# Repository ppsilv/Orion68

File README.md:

# Orion68
Orion68 a litle system for mc68000

-software

|--dev

|    |--kernel -----> Ambiente de compilação do kernel e de aplicações para o kernel usando libc_pic

|    |--orioncore---> Ambiente de compilação do orioncor e de aplicações para o orioncore usando libcbios nopic

|--include

|--lib

|--libs

     |--libc_pic
     
     |--libm68
     
     |--liborion

2025/10/12: aparentemente essa foi a última versão que kernel carregou e rodou duart.elf

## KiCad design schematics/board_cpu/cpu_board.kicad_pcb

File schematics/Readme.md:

Terminação Passiva no Backplane:

    Mantenha o barramento "limpo" nas placas periféricas.
    No final do barramento físico (Slot 9), coloque as redes resistivas de 10k.
    Isso garante que, mesmo com o Orion68K vazio, os sinais críticos de controle não fiquem flutuando.

A Interface de Disco (MIDE/IDE):

    Hardware: Dois 74HC245 fazendo a ponte entre o barramento de dados do 68000 e o conector IDE.
    Byte-Swap: Desenhe as conexões invertidas entre os 245 e o conector (D15-D8 do 68k no D7-D0 do IDE).
    Atenção: No esquema, coloque uma nota bem visível sobre essa inversão para que, no futuro, você saiba que o acesso aos registros de 8 bits do IDE será feito via endereços pares (UDS ativo).

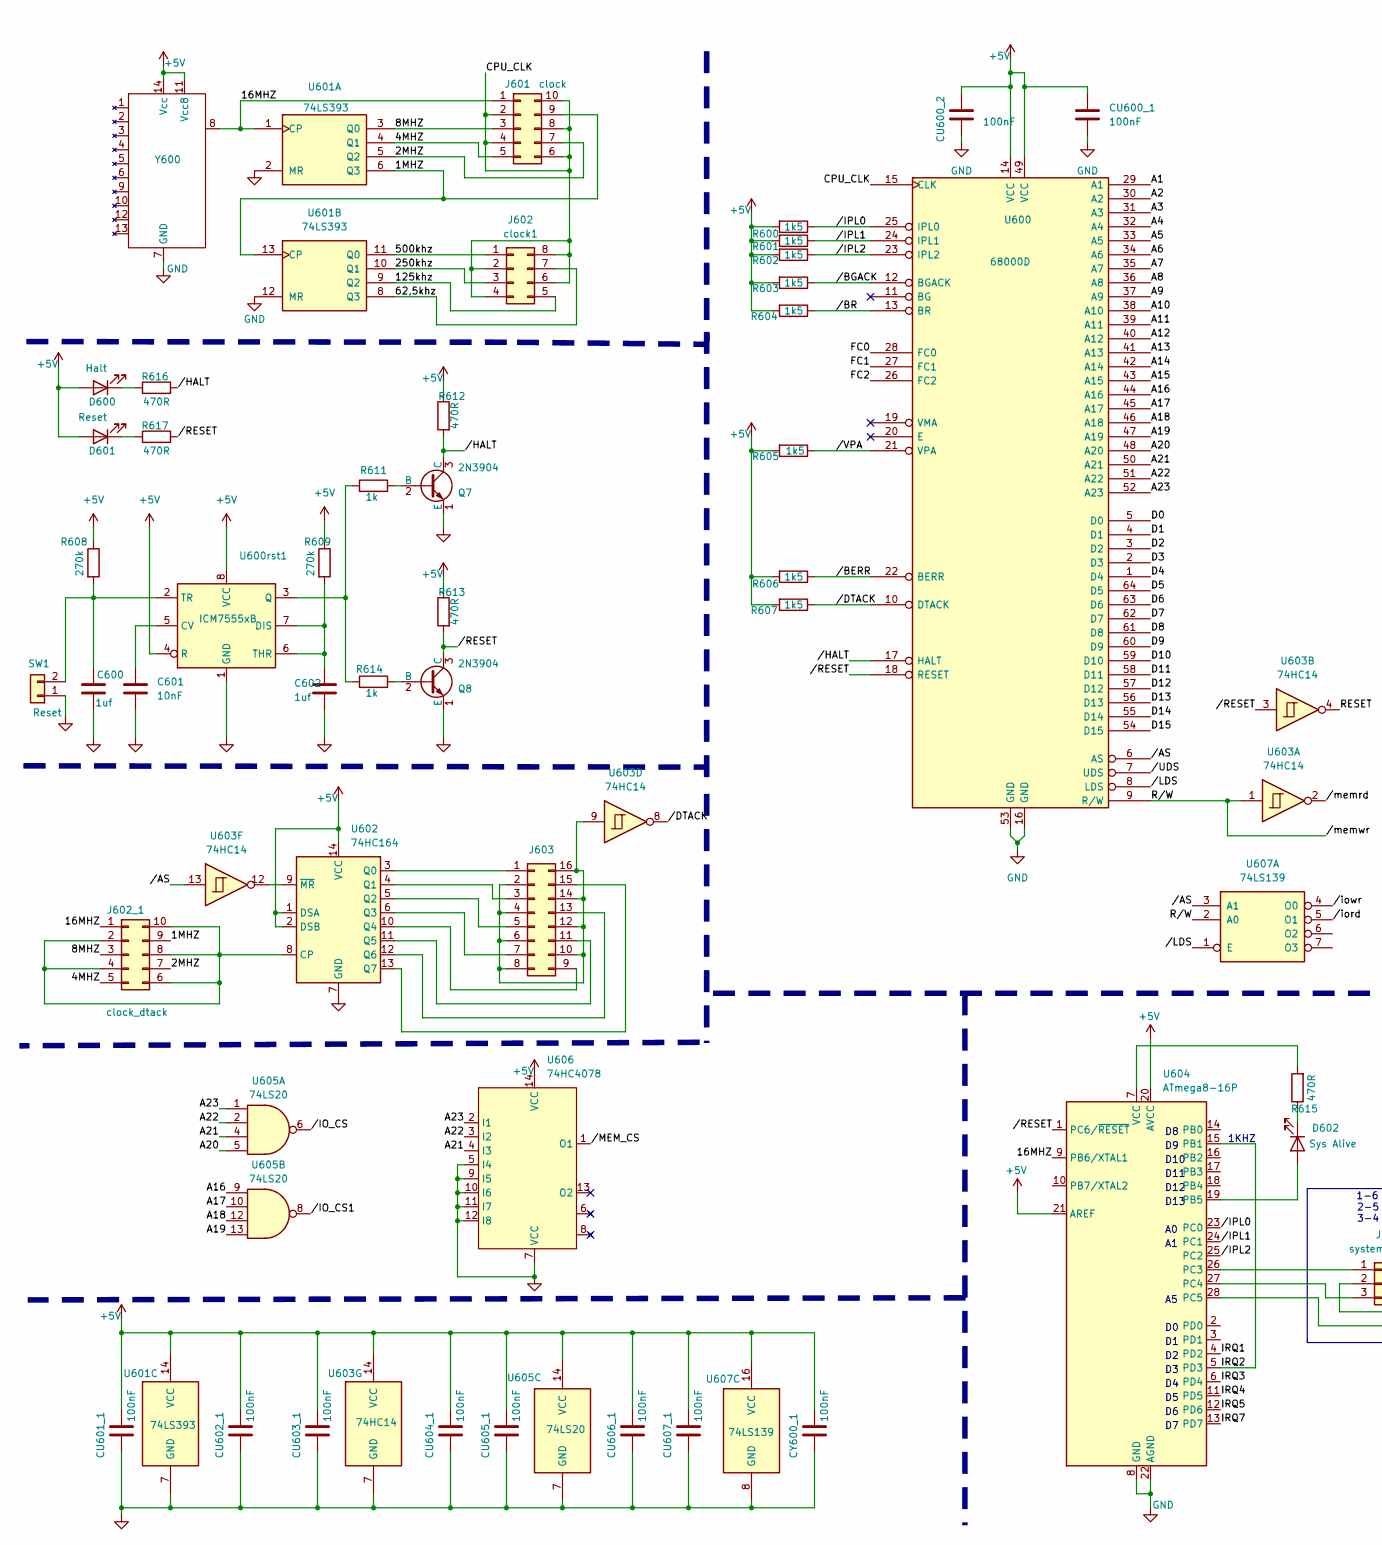
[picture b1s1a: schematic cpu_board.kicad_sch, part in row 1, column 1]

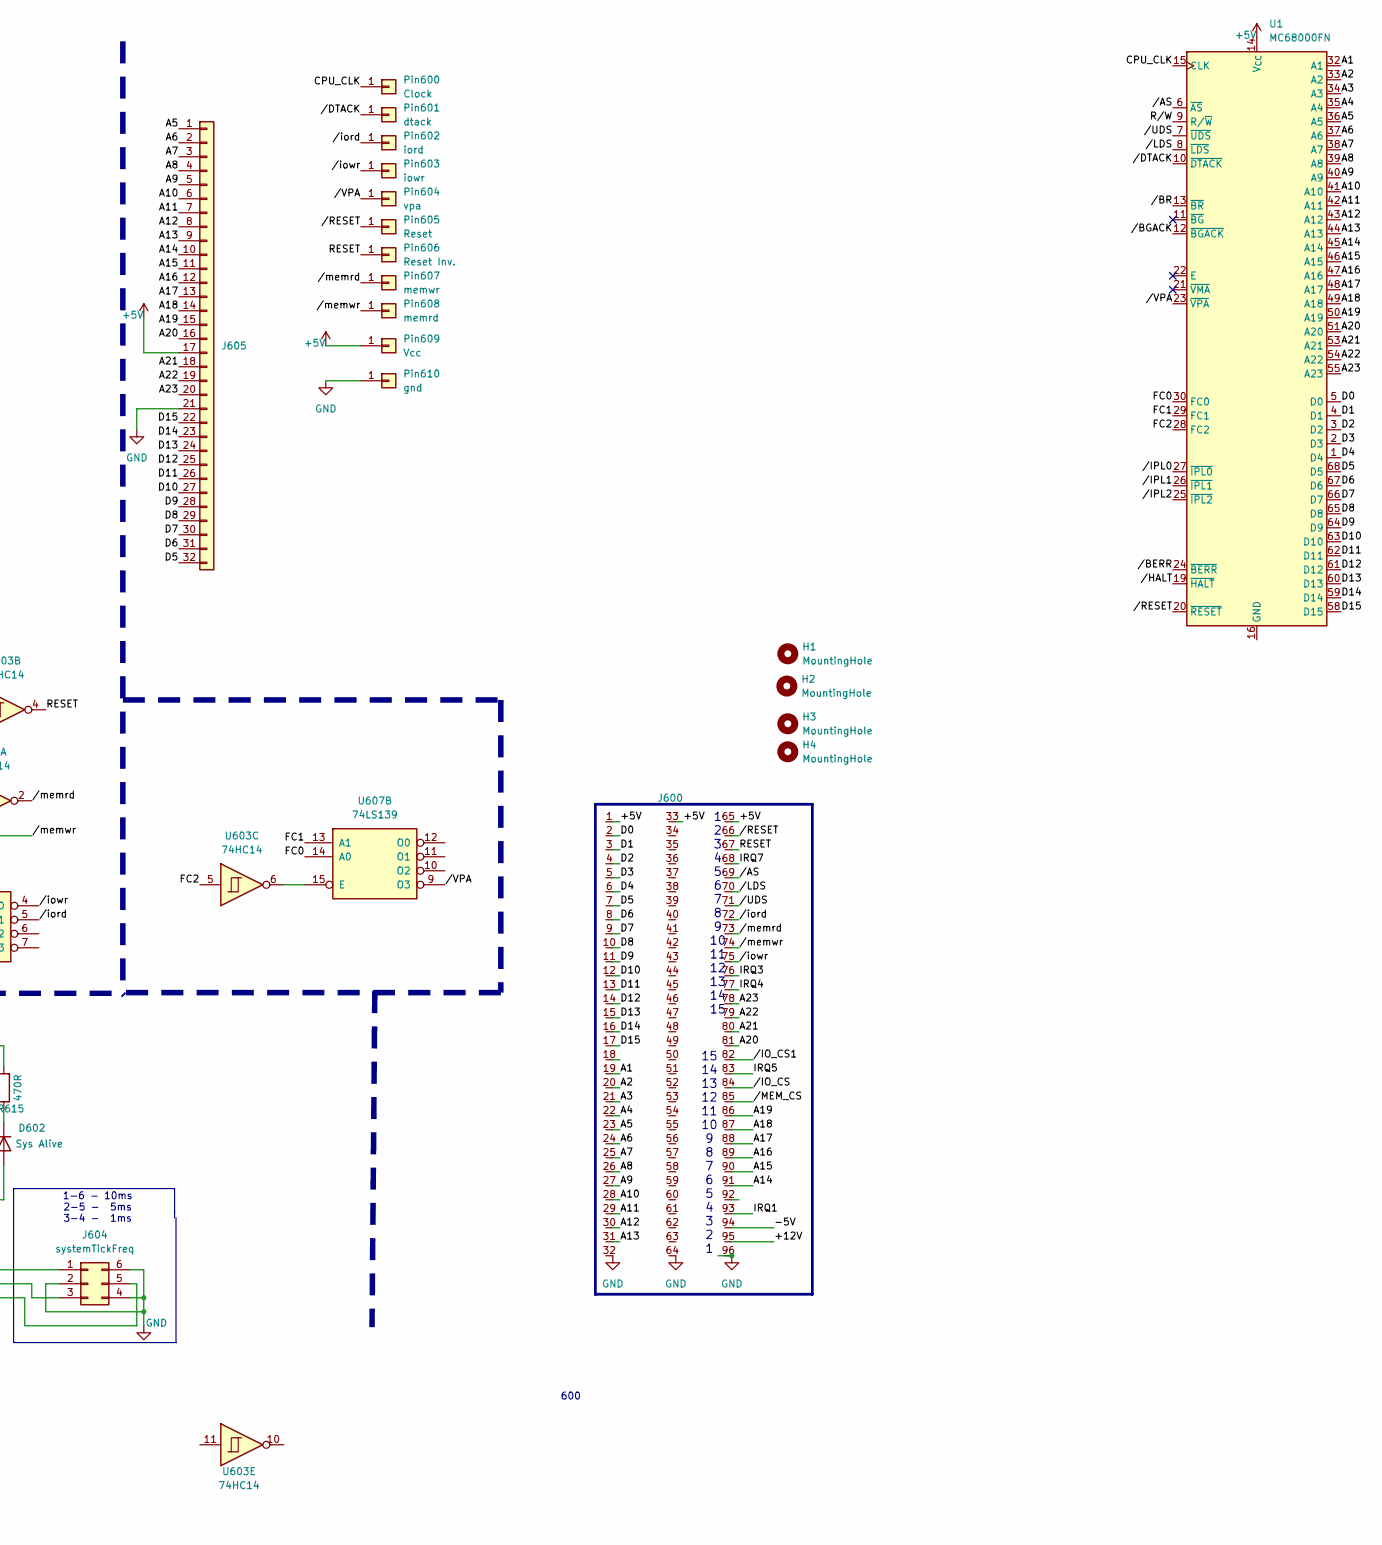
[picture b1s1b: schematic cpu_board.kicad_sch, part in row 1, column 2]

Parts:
C600, C602: 1uf; CP_Radial_D8.0mm_P3.50mm
C601: 10nF; C_0603_1608Metric
CU600_1, CU600_2, CU601_1, CU602_1, CU603_1, CU604_1, CU605_1, CU606_1, CU607_1: 100nF; C_0805_2012Metric
CY600_1: 100nF; C_0805_2012Metric
D600: Halt; PinHeader_1x02_P2.54mm_Vertical
D601: Reset; PinHeader_1x02_P2.54mm_Vertical
D602: Sys Alive; PinHeader_1x02_P2.54mm_Vertical
H1, H2: MountingHole; MountingHole_3.2mm_M3
H3, H4: MountingHole; MountingHole_2.1mm
J600: Euro96pin; conn_euro96
J601: clock; PinHeader_2x05_P2.54mm_Vertical
J602: clock1; PinHeader_2x04_P2.54mm_Vertical
J602_1: clock_dtack; PinHeader_2x05_P2.54mm_Vertical
J603: Conn_02x08_Counter_Clockwise; PinHeader_2x08_P2.54mm_Vertical
J604: systemTickFreq; PinHeader_2x03_P2.54mm_Vertical
J605: Conn_01x32; PinHeader_1x32_P2.54mm_Vertical
Pin600: Clock; PinHeader_1x01_P2.54mm_Vertical
Pin601: dtack; PinHeader_1x01_P2.54mm_Vertical
Pin602: iord; PinHeader_1x01_P2.54mm_Vertical
Pin603: iowr; PinHeader_1x01_P2.54mm_Vertical
Pin604: vpa; PinHeader_1x01_P2.54mm_Vertical
Pin605: Reset; PinHeader_1x01_P2.54mm_Vertical
Pin606: Reset Inv.; PinHeader_1x01_P2.54mm_Vertical
Pin607: memwr; PinHeader_1x01_P2.54mm_Vertical
Pin608: memrd; PinHeader_1x01_P2.54mm_Vertical
Pin609: Vcc; PinHeader_1x01_P2.54mm_Vertical
Pin610: gnd; PinHeader_1x01_P2.54mm_Vertical
Q7, Q8: 2N3904; TO-92_Inline
R600, R601, R602, R603, R604, R605, R606, R607: 1k5; R_0805_2012Metric
R608, R609: 270k; R_Axial_DIN0204_L3.6mm_D1.6mm_P5.08mm_Horizontal
R611, R614: 1k; R_Axial_DIN0204_L3.6mm_D1.6mm_P5.08mm_Horizontal
R612, R613, R615, R616, R617: 470R; R_Axial_DIN0204_L3.6mm_D1.6mm_P5.08mm_Horizontal
SW1: Reset; PinHeader_1x02_P2.54mm_Vertical
U1: MC68000FN; PLCC-68_THT-Socket
U600: 68000D; DIP-64_W22.86mm
U600rst1: ICM7555xB; DIP-8_W7.62mm
U601: 74LS393; DIP-14_W7.62mm
U602: 74HC164; DIP-14_W7.62mm
U603: 74HC14; DIP-14_W7.62mm
U604: ATmega8-16P; DIP-28_W7.62mm
U605: 74LS20; DIP-14_W7.62mm
U606: 74HC4078; DIP-14_W7.62mm
U607: 74LS139; DIP-16_W7.62mm
Y600: DIP-14_W7.62mm

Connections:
+5V: CU600_1.1, CU600_2.1, CU601_1.1, CU602_1.1, CU603_1.1, CU604_1.1, CU605_1.1, CU606_1.1, CU607_1.1, CY600_1.1, D600.2 (A), D601.2 (A), J600.1, J600.33, J600.65, J605.17, Pin609.1, R600.2, R601.2, R602.2, R603.2, R604.2, R605.2, R606.2, R607.2, R608.1, R609.1, R612.1, R613.1, U1.14 (V_{CC}), U1.52 (V_{CC}), U600.14 (VCC), U600.49 (VCC), U600rst1.4 (R), U600rst1.8 (VCC), U601.14 (VCC), U602.1 (DSA), U602.2 (DSB), U602.14 (VCC), U603.14 (VCC), U604.20 (AVCC), U604.21 (AREF), U605.14 (VCC), U606.14 (VCC), U607.16 (VCC), Y600.11 (Vcc8), Y600.14 (Vcc)
/1MHZ: J601.9, J602_1.9, U601.6 (Q3), U601.13 (CP)
/2MHZ: J601.7, J602_1.7, U601.5 (Q2)
/4MHZ: J601.5, J602_1.5, U601.4 (Q1)
/8MHZ: J601.3, J602_1.3, U601.3 (Q0)
/16MHZ: J601.1, J602_1.1, U601.1 (CP), U604.9 (PB6/XTAL1), Y600.8
/62,5khz: J602.7, U601.8 (Q3)
/125khz: J602.5, U601.9 (Q2)
/250khz: J602.3, U601.10 (Q1)
/500khz: J602.1, U601.11 (Q0)
/+12V: J600.95
/-5V: J600.94
/A1: J600.19, U1.32 (A1), U600.29 (A1)
/A2: J600.20, U1.33 (A2), U600.30 (A2)
/A3: J600.21, U1.34 (A3), U600.31 (A3)
/A4: J600.22, U1.35 (A4), U600.32 (A4)
/A5: J600.23, J605.1, U1.36 (A5), U600.33 (A5)
/A6: J600.24, J605.2, U1.37 (A6), U600.34 (A6)
/A7: J600.25, J605.3, U1.38 (A7), U600.35 (A7)
/A8: J600.26, J605.4, U1.39 (A8), U600.36 (A8)
/A9: J600.27, J605.5, U1.40 (A9), U600.37 (A9)
/A10: J600.28, J605.6, U1.41 (A10), U600.38 (A10)
/A11: J600.29, J605.7, U1.42 (A11), U600.39 (A11)
/A12: J600.30, J605.8, U1.43 (A12), U600.40 (A12)
/A13: J600.31, J605.9, U1.44 (A13), U600.41 (A13)
/A14: J600.91, J605.10, U1.45 (A14), U600.42 (A14)
/A15: J600.90, J605.11, U1.46 (A15), U600.43 (A15)
/A16: J600.89, J605.12, U1.47 (A16), U600.44 (A16), U605.9
/A17: J600.88, J605.13, U1.48 (A17), U600.45 (A17), U605.10
/A18: J600.87, J605.14, U1.49 (A18), U600.46 (A18), U605.12
/A19: J600.86, J605.15, U1.50 (A19), U600.47 (A19), U605.13
/A20: J600.81, J605.16, U1.51 (A20), U600.48 (A20), U605.5
/A21: J600.80, J605.18, U1.53 (A21), U600.50 (A21), U605.4, U606.4 (I3)
/A22: J600.79, J605.19, U1.54 (A22), U600.51 (A22), U605.2, U606.3 (I2)
/A23: J600.78, J605.20, U1.55 (A23), U600.52 (A23), U605.1, U606.2 (I1)
/CPU_CLK: J601.2, J601.4, J601.6, J601.8, J601.10, J602.2, J602.4, J602.6, J602.8, Pin600.1, U1.15 (CLK), U600.15 (CLK)
/D0: J600.2, U1.5 (D0), U600.5 (D0)
/D1: J600.3, U1.4 (D1), U600.4 (D1)
/D2: J600.4, U1.3 (D2), U600.3 (D2)
/D3: J600.5, U1.2 (D3), U600.2 (D3)
/D4: J600.6, U1.1 (D4), U600.1 (D4)
/D5: J600.7, J605.32, U1.68 (D5), U600.64 (D5)
/D6: J600.8, J605.31, U1.67 (D6), U600.63 (D6)
/D7: J600.9, J605.30, U1.66 (D7), U600.62 (D7)
/D8: J600.10, J605.29, U1.65 (D8), U600.61 (D8)
/D9: J600.11, J605.28, U1.64 (D9), U600.60 (D9)
/D10: J600.12, J605.27, U1.63 (D10), U600.59 (D10)
/D11: J600.13, J605.26, U1.62 (D11), U600.58 (D11)
/D12: J600.14, J605.25, U1.61 (D12), U600.57 (D12)
/D13: J600.15, J605.24, U1.60 (D13), U600.56 (D13)
/D14: J600.16, J605.23, U1.59 (D14), U600.55 (D14)
/D15: J600.17, J605.22, U1.58 (D15), U600.54 (D15)
/FC0: U1.30 (FC0), U600.28 (FC0), U607.14 (A0)
/FC1: U1.29 (FC1), U600.27 (FC1), U607.13 (A1)
/FC2: U1.28 (FC2), U600.26 (FC2), U603.5
/IRQ1: J600.93, U604.4 (PD2)
/IRQ2: U604.5 (PD3), U604.15 (PB1)
/IRQ3: J600.76, U604.6 (PD4)
/IRQ4: J600.77, U604.11 (PD5)
/IRQ5: J600.83, U604.12 (PD6)
/IRQ7: J600.68, U604.13 (PD7)
/RESET: J600.67, Pin606.1, U603.4
/R/W: J600.74, Pin608.1, U1.9 (R/~W), U600.9 (R/W), U603.1, U607.2 (A0)
//AS: J600.69, U1.6 (~AS), U600.6 (AS), U603.13, U607.3 (A1)
//BERR: R606.1, U1.24 (~BERR), U600.22 (BERR)
//BGACK: R603.1, U1.12 (~BGACK), U600.12 (BGACK)
//BR: R604.1, U1.13 (~BR), U600.13 (BR)
//DTACK: Pin601.1, R607.1, U1.10 (~DTACK), U600.10 (DTACK), U603.8
//HALT: Q7.3 (C), R612.2, R616.2, U1.19 (~HALT), U600.17 (HALT)
//IO_CS: J600.84, U605.6
//IO_CS1: J600.82, U605.8
//IPL0: R600.1, U1.27 (~IPL0), U600.25 (IPL0), U604.23 (PC0)
//IPL1: R601.1, U1.26 (~IPL1), U600.24 (IPL1), U604.24 (PC1)
//IPL2: R602.1, U1.25 (~IPL2), U600.23 (IPL2), U604.25 (PC2)
//LDS: J600.70, U1.8 (~LDS), U600.8 (LDS), U607.1 (E)
//MEM_CS: J600.85, U606.1 (O1)
//RESET: J600.66, Pin605.1, Q8.3 (C), R613.2, R617.2, U1.20 (~RESET), U600.18 (RESET), U603.3, U604.1 (PC6/~RESET)
//UDS: J600.71, U1.7 (~UDS), U600.7 (UDS)
//VPA: Pin604.1, R605.1, U1.23 (~VPA), U600.21 (VPA), U607.9 (O3)
//iord: J600.72, Pin602.1, U607.5 (O1)
//iowr: J600.75, Pin603.1, U607.4 (O0)
//memrd: J600.73, Pin607.1, U603.2
GND: C600.2, C601.2, C602.2, CU600_1.2, CU600_2.2, CU601_1.2, CU602_1.2, CU603_1.2, CU604_1.2, CU605_1.2, CU606_1.2, CU607_1.2, CY600_1.2, J600.32, J600.64, J600.96, J604.2, J604.4, J604.6, J605.21, Pin610.1, Q7.1 (E), Q8.1 (E), SW1.1, U600.16 (GND), U600.53 (GND), U600rst1.1 (GND), U601.2 (MR), U601.7 (GND), U601.12 (MR), U602.7 (GND), U603.7 (GND), U604.8 (GND), U604.22 (AGND), U605.7 (GND), U606.5 (I4), U606.7 (VCC), U606.9 (I5), U606.10 (I6), U606.11 (I7), U606.12 (I8), U607.8 (GND), Y600.7 (GND)
unnamed: D600.1 (K), R616.1
unnamed: D601.1 (K), R617.1
unnamed: D602.2 (A), U604.19 (PB5)
unnamed: D602.1 (K), R615.1
unnamed: J602_1.2, J602_1.4, J602_1.6, J602_1.8, J602_1.10, U602.8 (CP)
unnamed: J603.1, U602.3 (Q0)
unnamed: J603.3, U602.4 (Q1)
unnamed: J603.5, U602.5 (Q2)
unnamed: J603.7, U602.6 (Q3)
unnamed: J603.9, U602.10 (Q4)
unnamed: J603.2, J603.4, J603.6, J603.8, J603.10, J603.12, J603.14, J603.16, U603.9
unnamed: J603.11, U602.11 (Q5)
unnamed: J603.13, U602.12 (Q6)
unnamed: J603.15, U602.13 (Q7)
unnamed: J604.1, U604.26 (PC3)
unnamed: J604.3, U604.27 (PC4)
unnamed: J604.5, U604.28 (PC5)
unnamed: Q7.2 (B), R611.1
unnamed: Q8.2 (B), R614.1
unnamed: C600.1, R608.2, SW1.2, U600rst1.2 (TR)
unnamed: U1.16 (GND), U1.17 (GND), U1.56 (GND), U1.57 (GND)
unnamed: C601.1, U600rst1.5 (CV)
unnamed: C602.1, R609.2, U600rst1.6 (THR), U600rst1.7 (DIS)
unnamed: R611.2, R614.2, U600rst1.3 (Q)
unnamed: U602.9 (~MR), U603.12
unnamed: R615.2, U604.7 (VCC)
unnamed: U603.6, U607.15 (E)

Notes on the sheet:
1 2 3 4 5 6 7 8 9 10 11 12 13 14 15
15 14 13 12 11 10 9 8 7 6 5 4 3 2 1
600
1KHZ
D11
D13
1-6 - 10ms 2-5 - 5ms 3-4 - 1ms
D12
D10

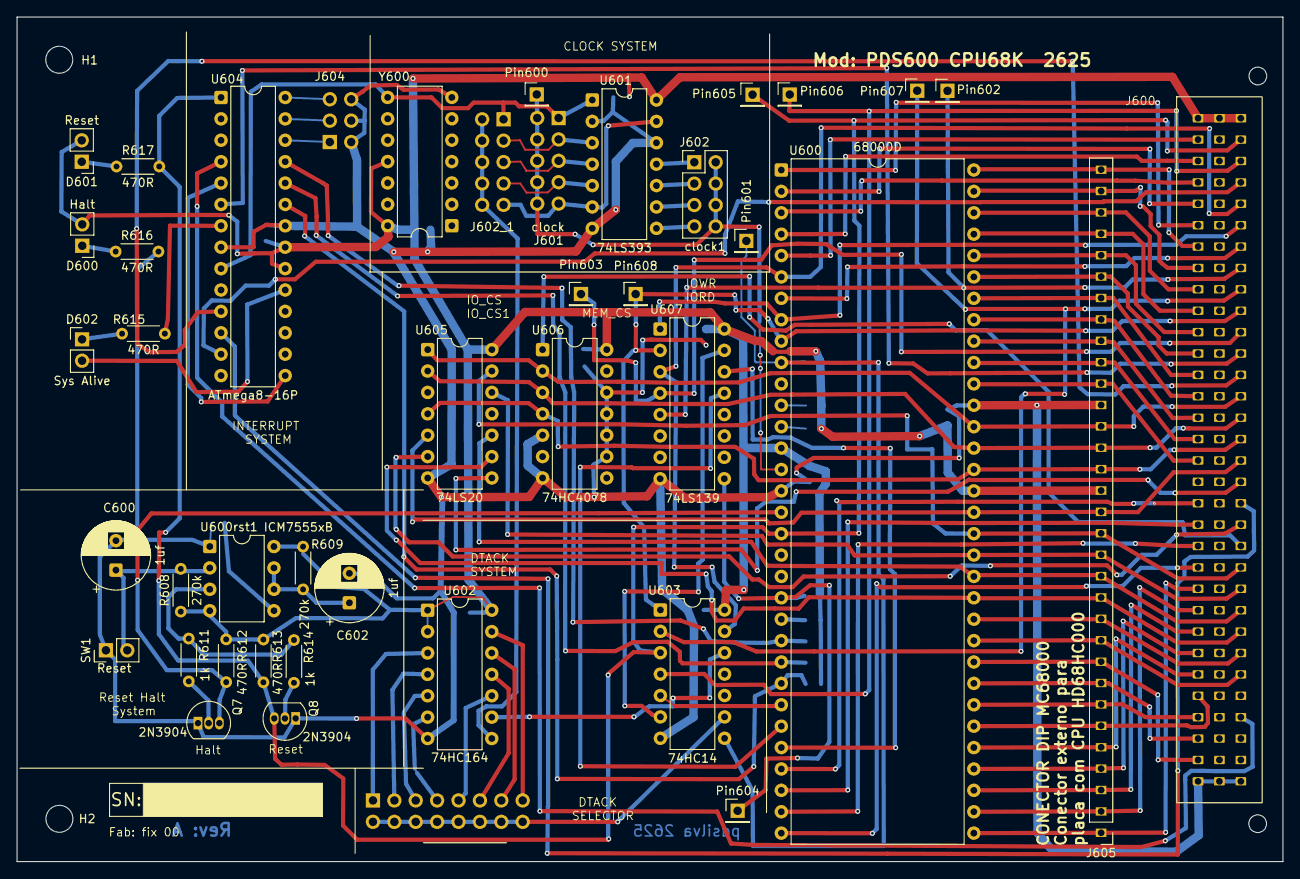
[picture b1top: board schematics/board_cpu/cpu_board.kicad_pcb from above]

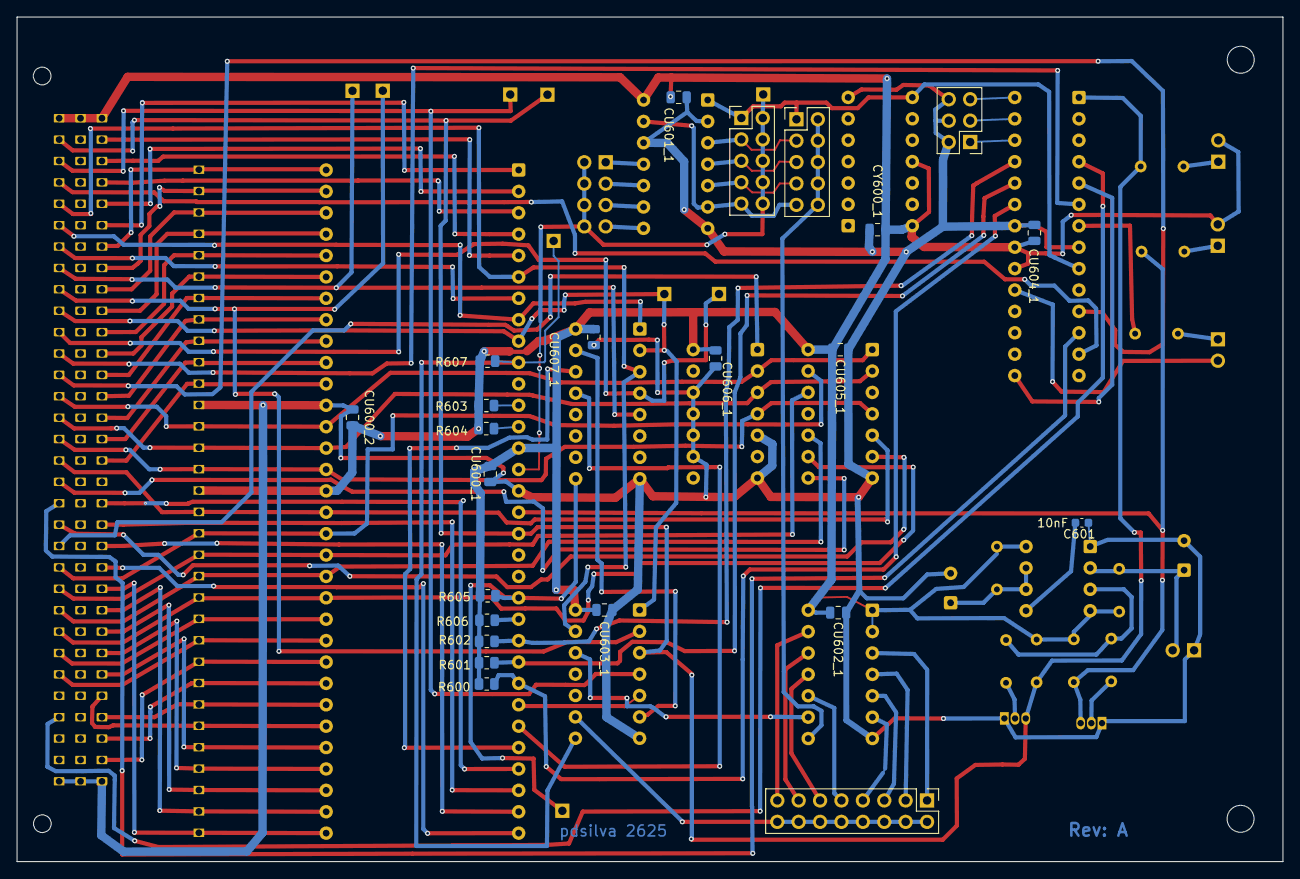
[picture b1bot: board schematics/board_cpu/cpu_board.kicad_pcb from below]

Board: 2 copper layers, 150.3 x 100.3 mm, 66 parts (23 on the bottom side), 107 nets.

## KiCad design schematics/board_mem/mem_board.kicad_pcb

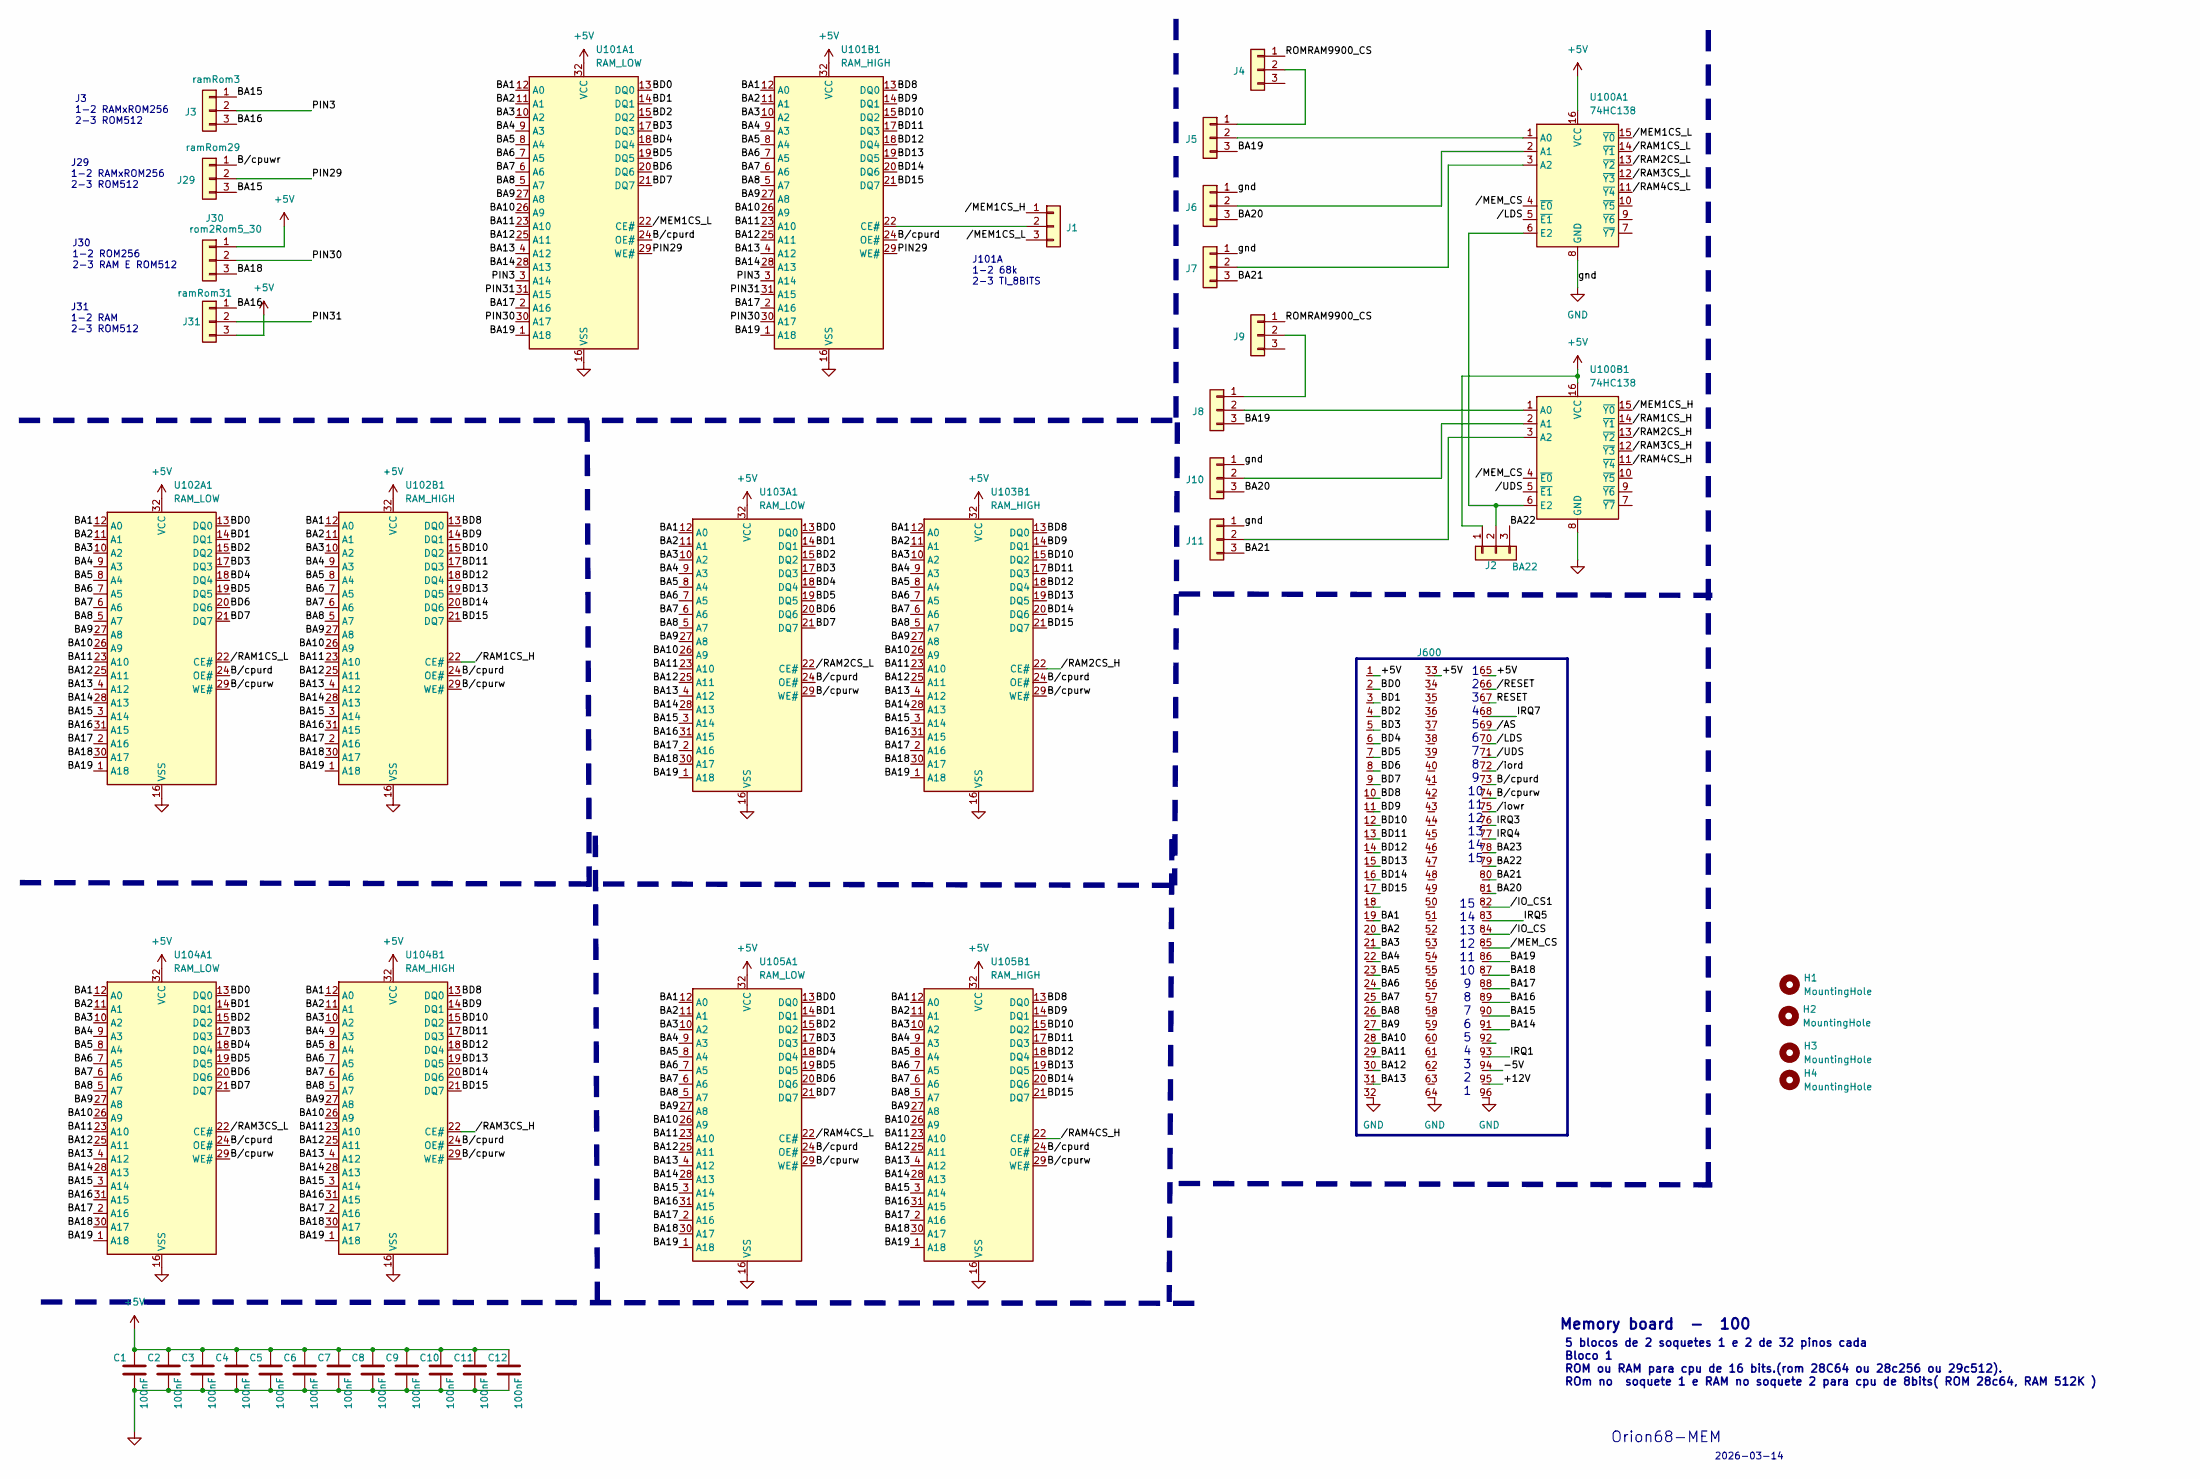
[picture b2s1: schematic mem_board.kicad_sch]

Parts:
C1, C2, C3, C4, C5, C6, C7, C8, C9, C10, C11, C12: 100nF; C_0805_2012Metric_Pad1.18x1.45mm_HandSolder
H1, H2: MountingHole; MountingHole_3.2mm_M3
H3, H4: MountingHole; MountingHole_2.1mm
J1: J101A; PinHeader_1x03_P2.54mm_Vertical
J2: BA22; PinHeader_1x03_P2.54mm_Vertical
J3: ramRom3; PinHeader_1x03_P2.54mm_Vertical
J4, J5, J8, J9: J100A; PinHeader_1x03_P2.54mm_Vertical
J6, J10: J100B; PinHeader_1x03_P2.54mm_Vertical
J7, J11: J100C; PinHeader_1x03_P2.54mm_Vertical
J29: ramRom29; PinHeader_1x03_P2.54mm_Vertical
J30: rom2Rom5_30; PinHeader_1x03_P2.54mm_Vertical
J31: ramRom31; PinHeader_1x03_P2.54mm_Vertical
J600: Euro96pin; conn_euro96
U100A1, U100B1: 74HC138; DIP-16_W7.62mm
U101A1, U102A1, U103A1, U104A1, U105A1: RAM_LOW; DIP-32_W15.24mm
U101B1, U102B1, U103B1, U104B1, U105B1: RAM_HIGH; DIP-32_W15.24mm

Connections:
+5V: C1.1, C2.1, C3.1, C4.1, C5.1, C6.1, C7.1, C8.1, C9.1, C10.1, C11.1, C12.1, J2.1, J30.1, J31.3, J600.1, J600.33, J600.65, U100A1.16 (VCC), U100B1.16 (VCC), U101A1.32 (VCC), U101B1.32 (VCC), U102A1.32 (VCC), U102B1.32 (VCC), U103A1.32 (VCC), U103B1.32 (VCC), U104A1.32 (VCC), U104B1.32 (VCC), U105A1.32 (VCC), U105B1.32 (VCC)
/+12V: J600.95
/-5V: J600.94
/BA1: J600.19, U101A1.12 (A0), U101B1.12 (A0), U102A1.12 (A0), U102B1.12 (A0), U103A1.12 (A0), U103B1.12 (A0), U104A1.12 (A0), U104B1.12 (A0), U105A1.12 (A0), U105B1.12 (A0)
/BA2: J600.20, U101A1.11 (A1), U101B1.11 (A1), U102A1.11 (A1), U102B1.11 (A1), U103A1.11 (A1), U103B1.11 (A1), U104A1.11 (A1), U104B1.11 (A1), U105A1.11 (A1), U105B1.11 (A1)
/BA3: J600.21, U101A1.10 (A2), U101B1.10 (A2), U102A1.10 (A2), U102B1.10 (A2), U103A1.10 (A2), U103B1.10 (A2), U104A1.10 (A2), U104B1.10 (A2), U105A1.10 (A2), U105B1.10 (A2)
/BA4: J600.22, U101A1.9 (A3), U101B1.9 (A3), U102A1.9 (A3), U102B1.9 (A3), U103A1.9 (A3), U103B1.9 (A3), U104A1.9 (A3), U104B1.9 (A3), U105A1.9 (A3), U105B1.9 (A3)
/BA5: J600.23, U101A1.8 (A4), U101B1.8 (A4), U102A1.8 (A4), U102B1.8 (A4), U103A1.8 (A4), U103B1.8 (A4), U104A1.8 (A4), U104B1.8 (A4), U105A1.8 (A4), U105B1.8 (A4)
/BA6: J600.24, U101A1.7 (A5), U101B1.7 (A5), U102A1.7 (A5), U102B1.7 (A5), U103A1.7 (A5), U103B1.7 (A5), U104A1.7 (A5), U104B1.7 (A5), U105A1.7 (A5), U105B1.7 (A5)
/BA7: J600.25, U101A1.6 (A6), U101B1.6 (A6), U102A1.6 (A6), U102B1.6 (A6), U103A1.6 (A6), U103B1.6 (A6), U104A1.6 (A6), U104B1.6 (A6), U105A1.6 (A6), U105B1.6 (A6)
/BA8: J600.26, U101A1.5 (A7), U101B1.5 (A7), U102A1.5 (A7), U102B1.5 (A7), U103A1.5 (A7), U103B1.5 (A7), U104A1.5 (A7), U104B1.5 (A7), U105A1.5 (A7), U105B1.5 (A7)
/BA9: J600.27, U101A1.27 (A8), U101B1.27 (A8), U102A1.27 (A8), U102B1.27 (A8), U103A1.27 (A8), U103B1.27 (A8), U104A1.27 (A8), U104B1.27 (A8), U105A1.27 (A8), U105B1.27 (A8)
/BA10: J600.28, U101A1.26 (A9), U101B1.26 (A9), U102A1.26 (A9), U102B1.26 (A9), U103A1.26 (A9), U103B1.26 (A9), U104A1.26 (A9), U104B1.26 (A9), U105A1.26 (A9), U105B1.26 (A9)
/BA11: J600.29, U101A1.23 (A10), U101B1.23 (A10), U102A1.23 (A10), U102B1.23 (A10), U103A1.23 (A10), U103B1.23 (A10), U104A1.23 (A10), U104B1.23 (A10), U105A1.23 (A10), U105B1.23 (A10)
/BA12: J600.30, U101A1.25 (A11), U101B1.25 (A11), U102A1.25 (A11), U102B1.25 (A11), U103A1.25 (A11), U103B1.25 (A11), U104A1.25 (A11), U104B1.25 (A11), U105A1.25 (A11), U105B1.25 (A11)
/BA13: J600.31, U101A1.4 (A12), U101B1.4 (A12), U102A1.4 (A12), U102B1.4 (A12), U103A1.4 (A12), U103B1.4 (A12), U104A1.4 (A12), U104B1.4 (A12), U105A1.4 (A12), U105B1.4 (A12)
/BA14: J600.91, U101A1.28 (A13), U101B1.28 (A13), U102A1.28 (A13), U102B1.28 (A13), U103A1.28 (A13), U103B1.28 (A13), U104A1.28 (A13), U104B1.28 (A13), U105A1.28 (A13), U105B1.28 (A13)
/BA15: J3.1, J29.3, J600.90, U102A1.3 (A14), U102B1.3 (A14), U103A1.3 (A14), U103B1.3 (A14), U104A1.3 (A14), U104B1.3 (A14), U105A1.3 (A14), U105B1.3 (A14)
/BA16: J3.3, J31.1, J600.89, U102A1.31 (A15), U102B1.31 (A15), U103A1.31 (A15), U103B1.31 (A15), U104A1.31 (A15), U104B1.31 (A15), U105A1.31 (A15), U105B1.31 (A15)
/BA17: J600.88, U101A1.2 (A16), U101B1.2 (A16), U102A1.2 (A16), U102B1.2 (A16), U103A1.2 (A16), U103B1.2 (A16), U104A1.2 (A16), U104B1.2 (A16), U105A1.2 (A16), U105B1.2 (A16)
/BA18: J30.3, J600.87, U102A1.30 (A17), U102B1.30 (A17), U103A1.30 (A17), U103B1.30 (A17), U104A1.30 (A17), U104B1.30 (A17), U105A1.30 (A17), U105B1.30 (A17)
/BA19: J5.3, J8.3, J600.86, U101A1.1 (A18), U101B1.1 (A18), U102A1.1 (A18), U102B1.1 (A18), U103A1.1 (A18), U103B1.1 (A18), U104A1.1 (A18), U104B1.1 (A18), U105A1.1 (A18), U105B1.1 (A18)
/BA20: J6.3, J10.3, J600.81
/BA21: J7.3, J11.3, J600.80
/BA22: J2.3, J600.79
/BA23: J600.78
/BD0: J600.2, U101A1.13 (DQ0), U102A1.13 (DQ0), U103A1.13 (DQ0), U104A1.13 (DQ0), U105A1.13 (DQ0)
/BD1: J600.3, U101A1.14 (DQ1), U102A1.14 (DQ1), U103A1.14 (DQ1), U104A1.14 (DQ1), U105A1.14 (DQ1)
/BD2: J600.4, U101A1.15 (DQ2), U102A1.15 (DQ2), U103A1.15 (DQ2), U104A1.15 (DQ2), U105A1.15 (DQ2)
/BD3: J600.5, U101A1.17 (DQ3), U102A1.17 (DQ3), U103A1.17 (DQ3), U104A1.17 (DQ3), U105A1.17 (DQ3)
/BD4: J600.6, U101A1.18 (DQ4), U102A1.18 (DQ4), U103A1.18 (DQ4), U104A1.18 (DQ4), U105A1.18 (DQ4)
/BD5: J600.7, U101A1.19 (DQ5), U102A1.19 (DQ5), U103A1.19 (DQ5), U104A1.19 (DQ5), U105A1.19 (DQ5)
/BD6: J600.8, U101A1.20 (DQ6), U102A1.20 (DQ6), U103A1.20 (DQ6), U104A1.20 (DQ6), U105A1.20 (DQ6)
/BD7: J600.9, U101A1.21 (DQ7), U102A1.21 (DQ7), U103A1.21 (DQ7), U104A1.21 (DQ7), U105A1.21 (DQ7)
/BD8: J600.10, U101B1.13 (DQ0), U102B1.13 (DQ0), U103B1.13 (DQ0), U104B1.13 (DQ0), U105B1.13 (DQ0)
/BD9: J600.11, U101B1.14 (DQ1), U102B1.14 (DQ1), U103B1.14 (DQ1), U104B1.14 (DQ1), U105B1.14 (DQ1)
/BD10: J600.12, U101B1.15 (DQ2), U102B1.15 (DQ2), U103B1.15 (DQ2), U104B1.15 (DQ2), U105B1.15 (DQ2)
/BD11: J600.13, U101B1.17 (DQ3), U102B1.17 (DQ3), U103B1.17 (DQ3), U104B1.17 (DQ3), U105B1.17 (DQ3)
/BD12: J600.14, U101B1.18 (DQ4), U102B1.18 (DQ4), U103B1.18 (DQ4), U104B1.18 (DQ4), U105B1.18 (DQ4)
/BD13: J600.15, U101B1.19 (DQ5), U102B1.19 (DQ5), U103B1.19 (DQ5), U104B1.19 (DQ5), U105B1.19 (DQ5)
/BD14: J600.16, U101B1.20 (DQ6), U102B1.20 (DQ6), U103B1.20 (DQ6), U104B1.20 (DQ6), U105B1.20 (DQ6)
/BD15: J600.17, U101B1.21 (DQ7), U102B1.21 (DQ7), U103B1.21 (DQ7), U104B1.21 (DQ7), U105B1.21 (DQ7)
/B/cpurd: J600.73, U101A1.24 (OE#), U101B1.24 (OE#), U102A1.24 (OE#), U102B1.24 (OE#), U103A1.24 (OE#), U103B1.24 (OE#), U104A1.24 (OE#), U104B1.24 (OE#), U105A1.24 (OE#), U105B1.24 (OE#)
/B/cpurw: J600.74, U102A1.29 (WE#), U102B1.29 (WE#), U103A1.29 (WE#), U103B1.29 (WE#), U104A1.29 (WE#), U104B1.29 (WE#), U105A1.29 (WE#), U105B1.29 (WE#)
/B/cpuwr: J29.1
/IRQ1: J600.93
/IRQ3: J600.76
/IRQ4: J600.77
/IRQ5: J600.83
/IRQ7: J600.68
/PIN3: J3.2, U101A1.3 (A14), U101B1.3 (A14)
/PIN29: J29.2, U101A1.29 (WE#), U101B1.29 (WE#)
/PIN30: J30.2, U101A1.30 (A17), U101B1.30 (A17)
/PIN31: J31.2, U101A1.31 (A15), U101B1.31 (A15)
/RESET: J600.67
/ROMRAM9900_CS: J4.1, J9.1
//AS: J600.69
//IO_CS: J600.84
//IO_CS1: J600.82
//LDS: J600.70, U100A1.5 (~E1)
//MEM1CS_H: J1.1, U100B1.15 (~Y0)
//MEM1CS_L: J1.3, U100A1.15 (~Y0), U101A1.22 (CE#)
//MEM_CS: J600.85, U100A1.4 (~E0), U100B1.4 (~E0)
//RAM1CS_H: U100B1.14 (~Y1), U102B1.22 (CE#)
//RAM1CS_L: U100A1.14 (~Y1), U102A1.22 (CE#)
//RAM2CS_H: U100B1.13 (~Y2), U103B1.22 (CE#)
//RAM2CS_L: U100A1.13 (~Y2), U103A1.22 (CE#)
//RAM3CS_H: U100B1.12 (~Y3), U104B1.22 (CE#)
//RAM3CS_L: U100A1.12 (~Y3), U104A1.22 (CE#)
//RAM4CS_H: U100B1.11 (~Y4), U105B1.22 (CE#)
//RAM4CS_L: U100A1.11 (~Y4), U105A1.22 (CE#)
//RESET: J600.66
//UDS: J600.71, U100B1.5 (~E1)
//iord: J600.72
//iowr: J600.75
GND: C1.2, C2.2, C3.2, C4.2, C5.2, C6.2, C7.2, C8.2, C9.2, C10.2, C11.2, C12.2, J6.1, J7.1, J10.1, J11.1, J600.32, J600.64, J600.96, U100A1.8 (GND), U100B1.8 (GND), U101A1.16 (VSS), U101B1.16 (VSS), U102A1.16 (VSS), U102B1.16 (VSS), U103A1.16 (VSS), U103B1.16 (VSS), U104A1.16 (VSS), U104B1.16 (VSS), U105A1.16 (VSS), U105B1.16 (VSS)
unnamed: J1.2, U101B1.22 (CE#)
unnamed: J2.2, U100A1.6 (E2), U100B1.6 (E2)
unnamed: J4.2, J5.1
unnamed: J5.2, U100A1.1 (A0)
unnamed: J6.2, U100A1.2 (A1)
unnamed: J7.2, U100A1.3 (A2)
unnamed: J8.1, J9.2
unnamed: J8.2, U100B1.1 (A0)
unnamed: J10.2, U100B1.2 (A1)
unnamed: J11.2, U100B1.3 (A2)

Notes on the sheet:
J3 1-2 RAMxROM256 2-3 ROM512
J29 1-2 RAMxROM256 2-3 ROM512
15 14 13 12 11 10 9 8 7 6 5 4 3 2 1
Memory board - 100
J31 1-2 RAM 2-3 ROM512
J101A 1-2 68k 2-3 TI_8BITS
2026-03-14
1 2 3 4 5 6 7 8 9 10 11 12 13 14 15
Orion68-MEM
5 blocos de 2 soquetes 1 e 2 de 32 pinos cada Bloco 1 ROM ou RAM para cpu de 16 bits.(rom 28C64 ou 28c256 ou 29c512). ROm no soquete 1 e RAM no soquete 2 para cpu de 8bits( ROM 28c64, RAM 512K )
J30 1-2 ROM256 2-3 RAM E ROM512

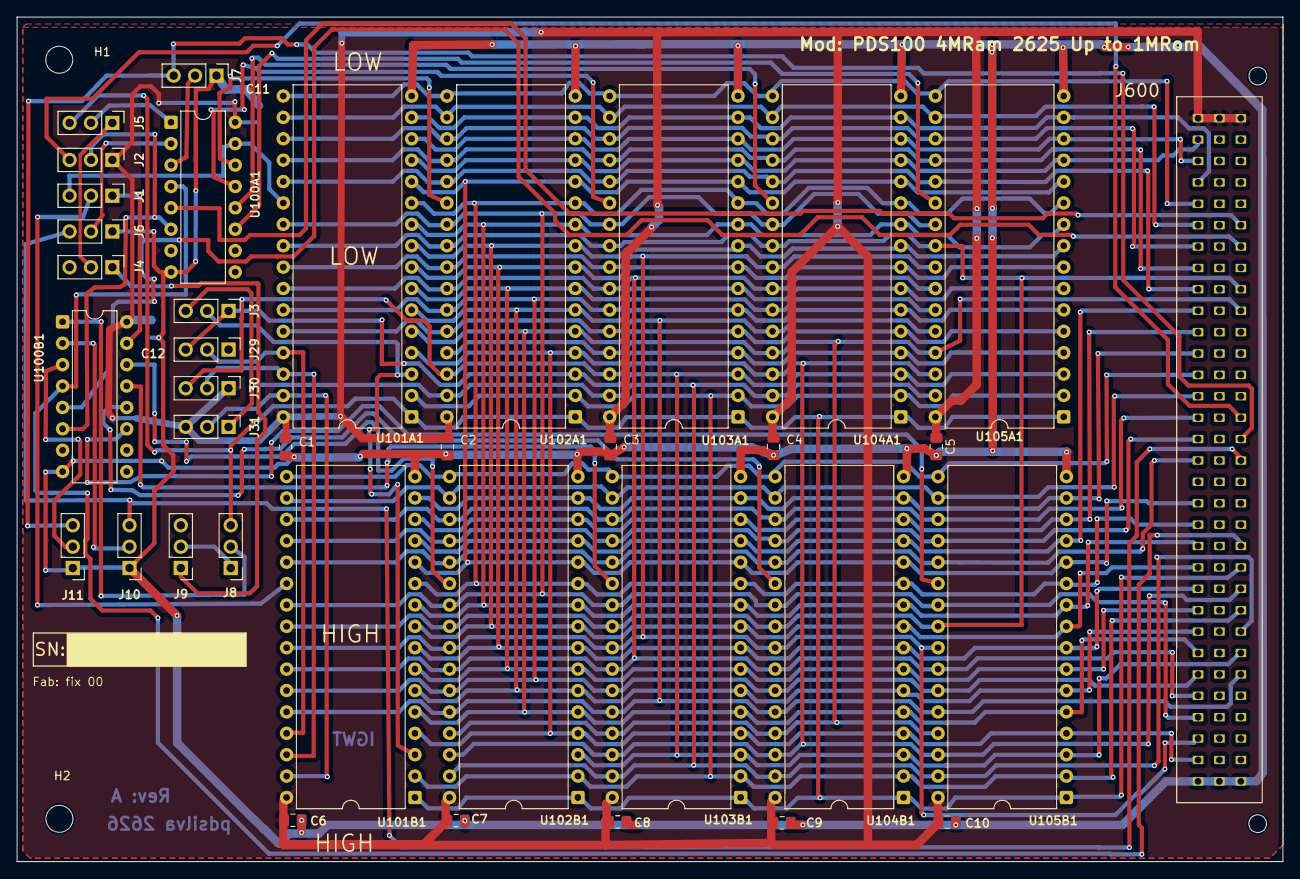
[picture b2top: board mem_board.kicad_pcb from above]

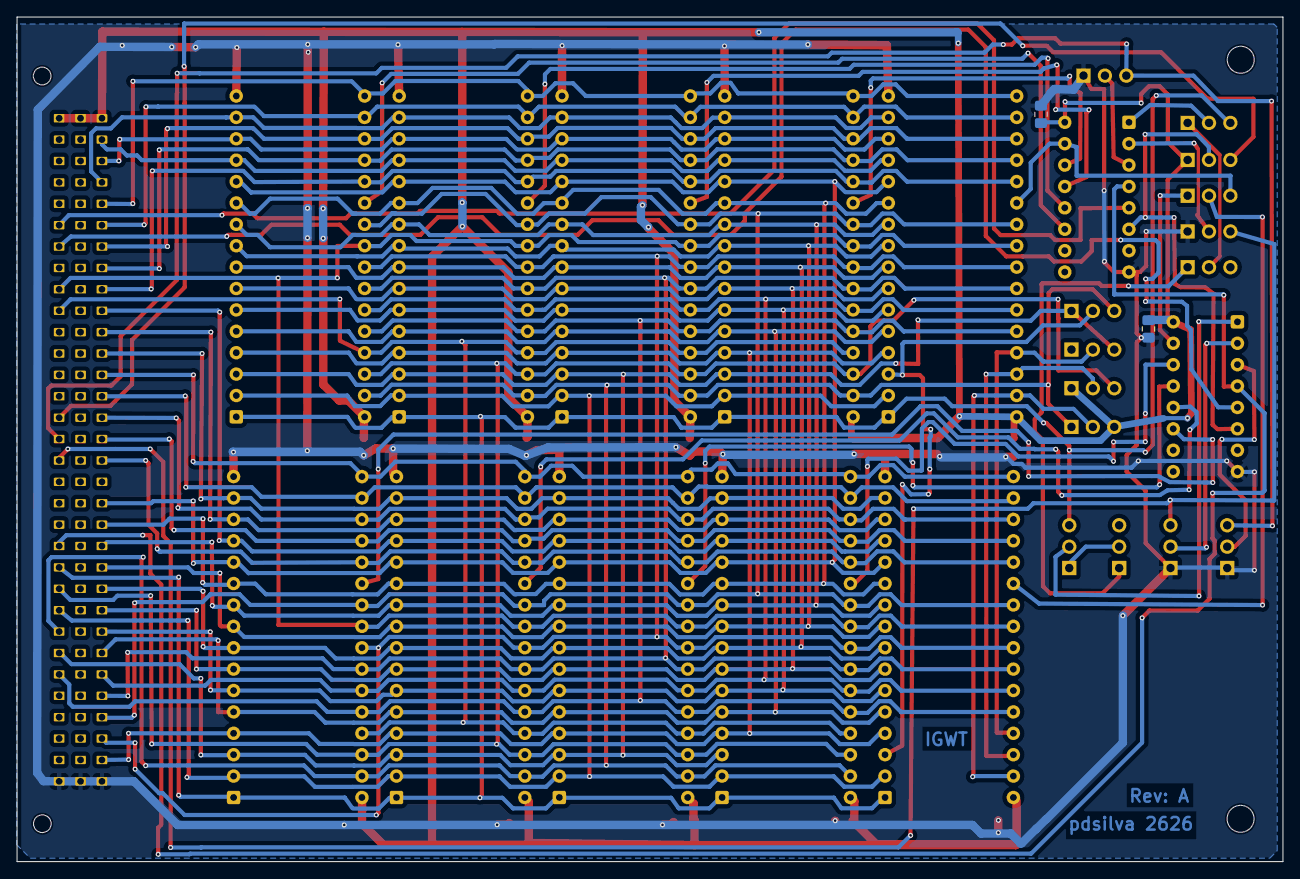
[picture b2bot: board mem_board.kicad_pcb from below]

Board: 2 copper layers, 150.3 x 100.3 mm, 43 parts (2 on the bottom side), 70 nets.
